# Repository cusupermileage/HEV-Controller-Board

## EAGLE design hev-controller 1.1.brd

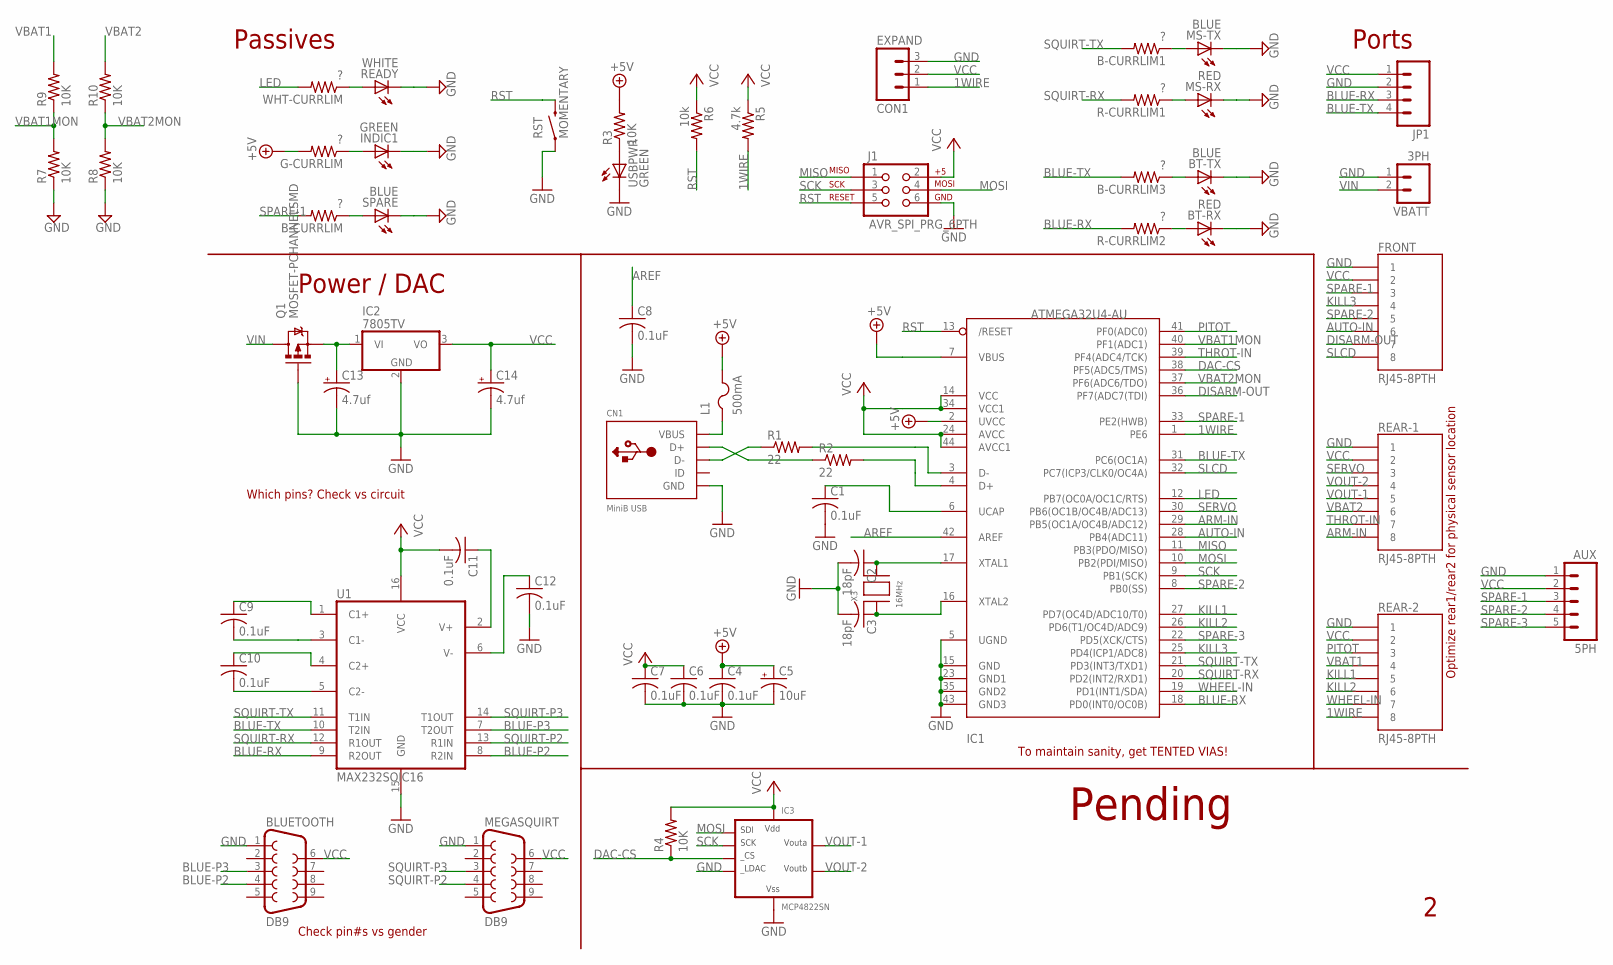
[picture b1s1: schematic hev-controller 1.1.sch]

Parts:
5PH: AUX; 1X05
B-CURRLIM, B-CURRLIM1, B-CURRLIM3: ?; R0805
BLUETOOTH: DB9
BT-RX: RED; CHIPLED_0805
BT-TX: BLUE; CHIPLED_0805
C1, C4, C6, C7, C8, C9, C10, C11, C12: 0.1uF; C0805K
C2, C3: 18pF; C0805K
C5: 10uF; A/3216-18R
C13, C14: 4.7uf; E2,5-6
CN1: MiniB USB; USB-MINIB
EXPAND: CON1; MOLEX-1X3
FRONT: RJ45-8PTH; RJ45-8
G-CURRLIM: ?; R0805
IC1: ATMEGA32U4-AU; TQFP44
IC2: 7805TV; TO220V
IC3: MCP4822SN; SO-08
INDIC1: GREEN; CHIPLED_0805
J1: AVR_SPI_PRG_6PTH; 2X3
JP1: M04PTH; 1X04
L1: 500mA; R1206
MEGASQUIRT: DB9
MS-RX: RED; CHIPLED_0805
MS-TX: BLUE; CHIPLED_0805
Q1: MOSFET-PCHANNELSMD; SOT23-3
R1, R2: 22; R0805
R3, R4, R7, R8, R9, R10: 10K; R0805
R5: 4.7k; R0805
R6: 10k; R0805
R-CURRLIM1, R-CURRLIM2: ?; R0805
READY: WHITE; LED-1206
REAR-1, REAR-2: RJ45-8PTH; RJ45-8
RST: MOMENTARY; TACTILE-SWITCH-1101NE
SPARE: BLUE; CHIPLED_0805
U1: MAX232SOIC16; SO016
USBPWR: GREEN; CHIPLED_0805
VBATT: 3PH; SCREWTERMINAL-3.5MM-2
WHT-CURRLIM: ?; R0805
X3: 16MHz; NX5032

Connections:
1WIRE: EXPAND.1, IC1.1 (PE6), R5.2, REAR-2.8
+5V: C4.1, C5.+, G-CURRLIM.2, IC1.2 (UVCC), IC1.7 (VBUS), L1.2, R3.2
AREF: C8.1, IC1.42 (AREF)
ARM-IN: IC1.29 (PB5(OC1A/OC4B/ADC12)), REAR-1.8
AUTO-IN: FRONT.6, IC1.28 (PB4(ADC11))
BLUE-P2: BLUETOOTH.4, U1.8 (R2IN)
BLUE-P3: BLUETOOTH.3, U1.7 (T2OUT)
BLUE-RX: IC1.18 (PD0(INT0/OC0B)), JP1.3, R-CURRLIM2.2, U1.9 (R2OUT)
BLUE-TX: B-CURRLIM3.2, IC1.31 (PC6(OC1A)), JP1.4, U1.10 (T2IN)
DAC-CS: IC1.38 (PF5(ADC5/TMS)), IC3.2 (CS), R4.1
DISARM-OUT: FRONT.7, IC1.36 (PF7(ADC7(TDI))
GND: 5PH.1, BLUETOOTH.1, BT-RX.C, BT-TX.C, C1.2, C2.2, C3.2, C4.2, C5.-, C6.2, C7.2, C8.2, C12.2, C13.-, C14.-, CN1.GND, EXPAND.3, FRONT.1, IC1.5 (UGND), IC1.15 (GND), IC1.23 (GND1), IC1.35 (GND2), IC1.43 (GND3), IC2.2 (GND), IC3.5 (LDAC), IC3.7 (VSS), INDIC1.C, J1.6, JP1.2, MEGASQUIRT.1, MS-RX.C, MS-TX.C, Q1.1 (G), R7.1, R8.1, READY.C, REAR-1.1, REAR-2.1, RST.P$1 (1), SPARE.C, U1.15 (GND), USBPWR.C, VBATT.1
KILL1: IC1.27 (PD7(OC4D/ADC10/T0)), REAR-2.5
KILL2: IC1.26 (PD6(T1/OC4D/ADC9)), REAR-2.6
KILL3: FRONT.4, IC1.25 (PD4(ICP1/ADC8))
LED: IC1.12 (PB7(OC0A/OC1C/RTS)), WHT-CURRLIM.2
MISO: IC1.11 (PB3(PDO/MISO)), J1.1
MOSI: IC1.10 (PB2(PDI/MISO)), IC3.4 (SDI), J1.4
unnamed: R3.1, USBPWR.A
unnamed: CN1.D+, R2.1
unnamed: IC1.3 (D-), R1.2
unnamed: IC1.4 (D+), R2.2
unnamed: CN1.D-, R1.1
unnamed: B-CURRLIM.1, SPARE.A
unnamed: G-CURRLIM.1, INDIC1.A
unnamed: C2.1, IC1.17 (XTAL1), X3.P$2
unnamed: C3.1, IC1.16 (XTAL2), X3.P$1
unnamed: B-CURRLIM1.1, MS-TX.A
unnamed: MS-RX.A, R-CURRLIM1.1
unnamed: B-CURRLIM3.1, BT-TX.A
unnamed: BT-RX.A, R-CURRLIM2.1
unnamed: C13.+, IC2.1 (VI), Q1.2 (S)
unnamed: READY.A, WHT-CURRLIM.1
unnamed: C9.1, U1.1 (C1+)
unnamed: C9.2, U1.3 (C1-)
unnamed: C10.1, U1.4 (C2+)
unnamed: C10.2, U1.5 (C2-)
unnamed: C11.1, U1.2 (V+)
unnamed: C12.1, U1.6 (V-)
PITOT: IC1.41 (PF0(ADC0)), REAR-2.3
RST: IC1.13 (/RESET), J1.5, R6.2, RST.P$2 (2)
SCK: IC1.9 (PB1(SCK)), IC3.3 (SCK), J1.3
SERVO: IC1.30 (PB6(OC1B/OC4B/ADC13)), REAR-1.3
SLCD: FRONT.8, IC1.32 (PC7(ICP3/CLK0/OC4A))
SPARE-1: 5PH.3, B-CURRLIM.2, FRONT.3, IC1.33 (PE2(HWB))
SPARE-2: 5PH.4, FRONT.5, IC1.8 (PB0(SS))
SPARE-3: 5PH.5, IC1.22 (PD5(XCK/CTS))
SQUIRT-P2: MEGASQUIRT.4, U1.13 (R1IN)
SQUIRT-P3: MEGASQUIRT.3, U1.14 (T1OUT)
SQUIRT-RX: IC1.20 (PD2(INT2/RXD1)), R-CURRLIM1.2, U1.12 (R1OUT)
SQUIRT-TX: B-CURRLIM1.2, IC1.21 (PD3(INT3/TXD1)), U1.11 (T1IN)
THROT-IN: IC1.39 (PF4(ADC4/TCK)), REAR-1.7
UCAP: C1.1, IC1.6 (UCAP)
VBAT1: R9.2, REAR-2.4
VBAT1MON: IC1.40 (PF1(ADC1)), R7.2, R9.1
VBAT2: R10.2, REAR-1.6
VBAT2MON: IC1.37 (PF6(ADC6/TDO)), R8.2, R10.1
VBUS: CN1.VBUS, L1.1
VCC: 5PH.2, BLUETOOTH.6, C6.1, C7.1, C11.2, C14.+, EXPAND.2, FRONT.2, IC1.14 (VCC), IC1.24 (AVCC), IC1.34 (VCC1), IC1.44 (AVCC1), IC2.3 (VO), IC3.1 (VDD), J1.2, JP1.1, MEGASQUIRT.6, R4.2, R5.1, R6.1, REAR-1.2, REAR-2.2, U1.16 (VCC)
VIN: Q1.3 (D), VBATT.2
VOUT-1: IC3.8 (VOUTA), REAR-1.5
VOUT-2: IC3.6 (VOUTB), REAR-1.4
WHEEL-IN: IC1.19 (PD1(INT1/SDA)), REAR-2.7

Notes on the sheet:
Ports
Passives
Power / DAC
Pending
Check pin#s vs gender
Which pins? Check vs circuit
Optimize rear1/rear2 for physical sensor location
To maintain sanity, get TENTED VIAS!

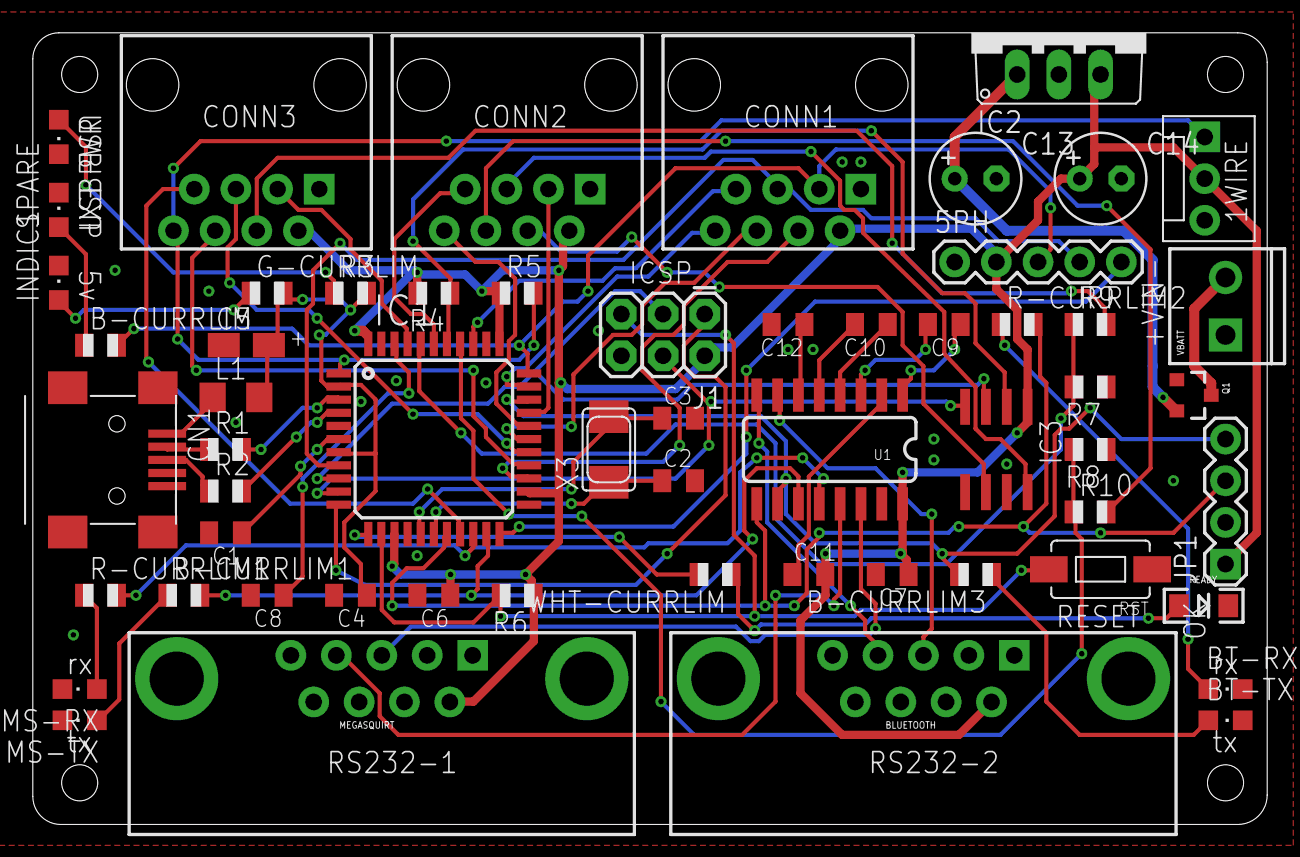
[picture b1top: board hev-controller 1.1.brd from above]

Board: 2 copper layers, 75.2 x 48.3 mm, 59 parts (1 on the bottom side), 63 nets.

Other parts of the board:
U$2: SUPERMILEAGE-SILK-V1.1

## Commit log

2014-03-20 Inital Check-In
2014-03-20 Upgrade to 1.1

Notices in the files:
parts and their libraries:
SparkFun-DiscreteSemi: Licensing: CC v3.0 Share-Alike You are welcome to use this library for commercial purposes.
